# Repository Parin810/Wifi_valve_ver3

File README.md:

### Solar Harvesting IoT based Irrigation valve:
This repo contains all the necessary hardware and software information about IoT/Wifi Actuator that has the following features:
1. ESP8266 as the controller/radio chip 
2. Uses MQTT as the communication protocol
3. BQ24210 or MCP73831 based solar harvestor
4. Uses Nodemcu custom build firmware
5. Auto modem sleep enabed (DTIM3,4,5)
6. The valve used is a latching solenoid 
7. DRV8832 as driver for latching solenoid
## Resources
The cheapst SOC that supports IEEE 802.11 standard
[ESP8266](https://tttapa.github.io/ESP8266/Chap04%20-%20Microcontroller.html)

Lua based firmware to simplify application programming
[Nodemcu - Lua](https://nodemcu.readthedocs.io/en/master/)

ESP8266 power consumption
[ESP8266 current profile](https://jeelabs.org/book/1526f/)

## Major Components Used 
(click to see datasheet)

[ESP8266-07](https://www.mikrocontroller.net/attachment/338570/Ai-thinker_ESP-07_WIFI_Module-EN.pdf)

LDO
[AP2112](https://www.diodes.com/assets/Datasheets/AP2112.pdf)

Lipo/ion charger
[MCP73831](http://ww1.microchip.com/downloads/en/DeviceDoc/20001984g.pdf)

Solar lipo/ion charger 
[BQ24210](http://www.ti.com/lit/ds/symlink/bq24210.pdf)

PMOS switch 
[PMV65XP](https://assets.nexperia.com/documents/data-sheet/PMV65XP.pdf)

## Loading LUA firmware
Download Nodemcu flasher from [here](https://github.com/nodemcu/nodemcu-flasher). for windows. For Linux use esptool.py (see repository for details)
Look at this [page](https://nodemcu.readthedocs.io/en/master/en/flash/) from nodemcu lua documentation

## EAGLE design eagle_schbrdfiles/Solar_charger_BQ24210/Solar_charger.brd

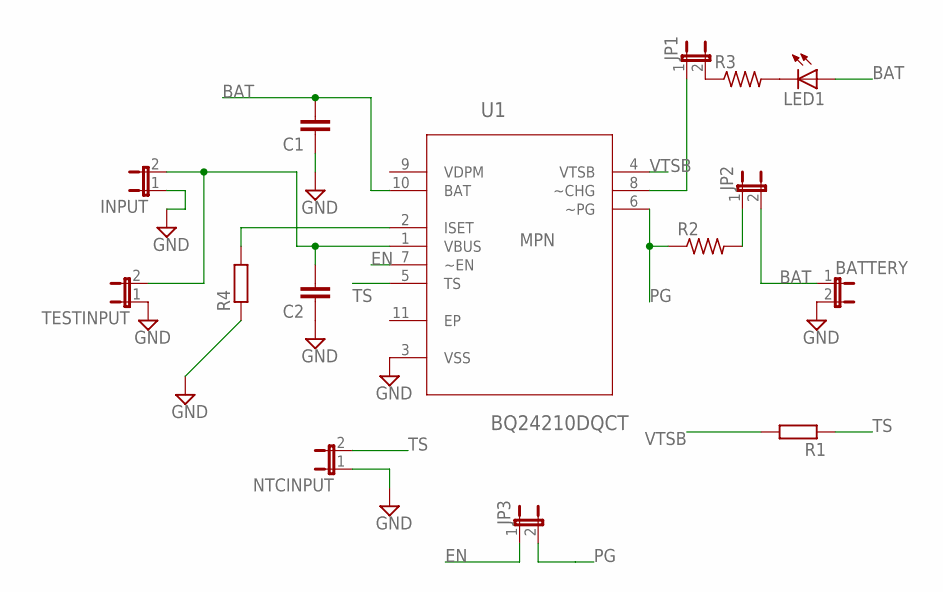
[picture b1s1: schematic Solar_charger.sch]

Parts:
BATTERY: JP1E; JP1
C1, C2: C2,5-3; C2.5-3
INPUT: JP1E; JP1
JP1, JP2, JP3: JP1E; JP1
LED1: LED5MM
NTCINPUT: JP1E; JP1
R1, R4: R-EU_0204/7; 0204/7
R2, R3: R-US_M1206; M1206
TESTINPUT: JP1E; JP1
U1: BQ24210DQCT; SON50P200X300X80-11N

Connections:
BAT: BATTERY.1, C1.2, JP2.2, LED1.A, U1.10 (BAT)
EN: JP3.1, U1.7 (~EN)
GND: BATTERY.2, C1.1, C2.1, INPUT.1, NTCINPUT.1, R4.1, U1.3 (VSS)
unnamed: C2.2, INPUT.2, TESTINPUT.2, U1.1 (VBUS)
unnamed: R4.2, U1.2 (ISET)
unnamed: JP2.1, R2.2
unnamed: LED1.K (C), R3.2
unnamed: JP1.1, U1.8 (~CHG)
unnamed: JP1.2, R3.1
PG: JP3.2, R2.1, U1.6 (~PG)
TS: NTCINPUT.2, R1.1, U1.5 (TS)
VTSB: R1.2, U1.4 (VTSB)

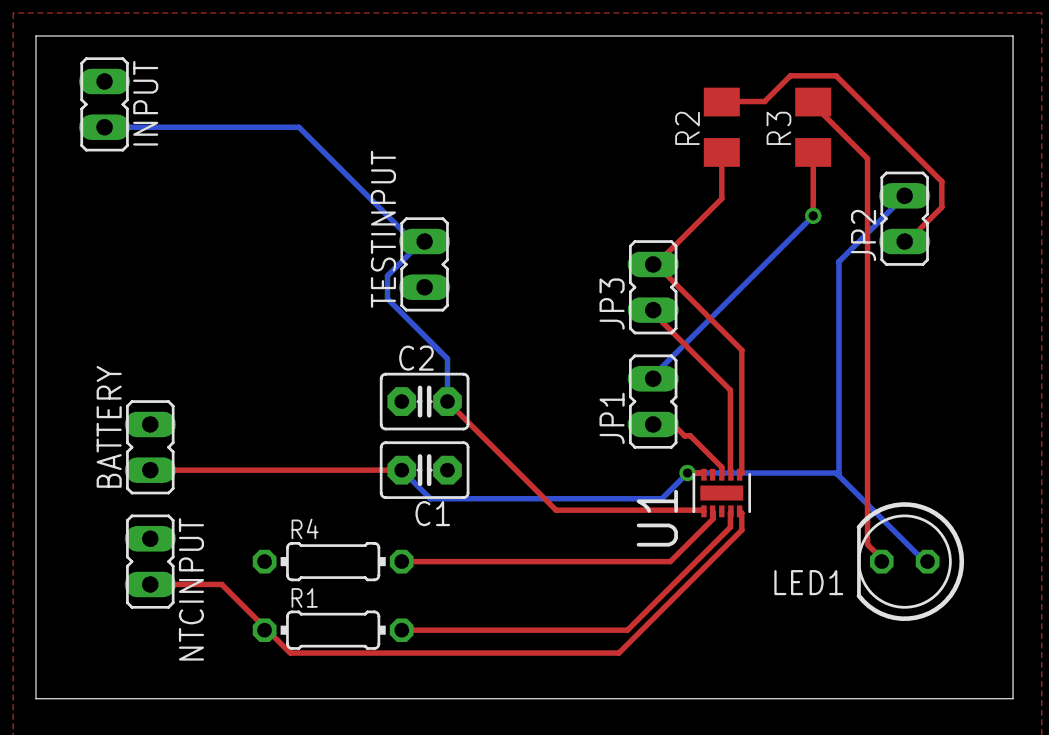
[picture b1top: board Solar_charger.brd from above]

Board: 2 copper layers, 54.3 x 36.8 mm, 15 parts (0 on the bottom side), 12 nets.

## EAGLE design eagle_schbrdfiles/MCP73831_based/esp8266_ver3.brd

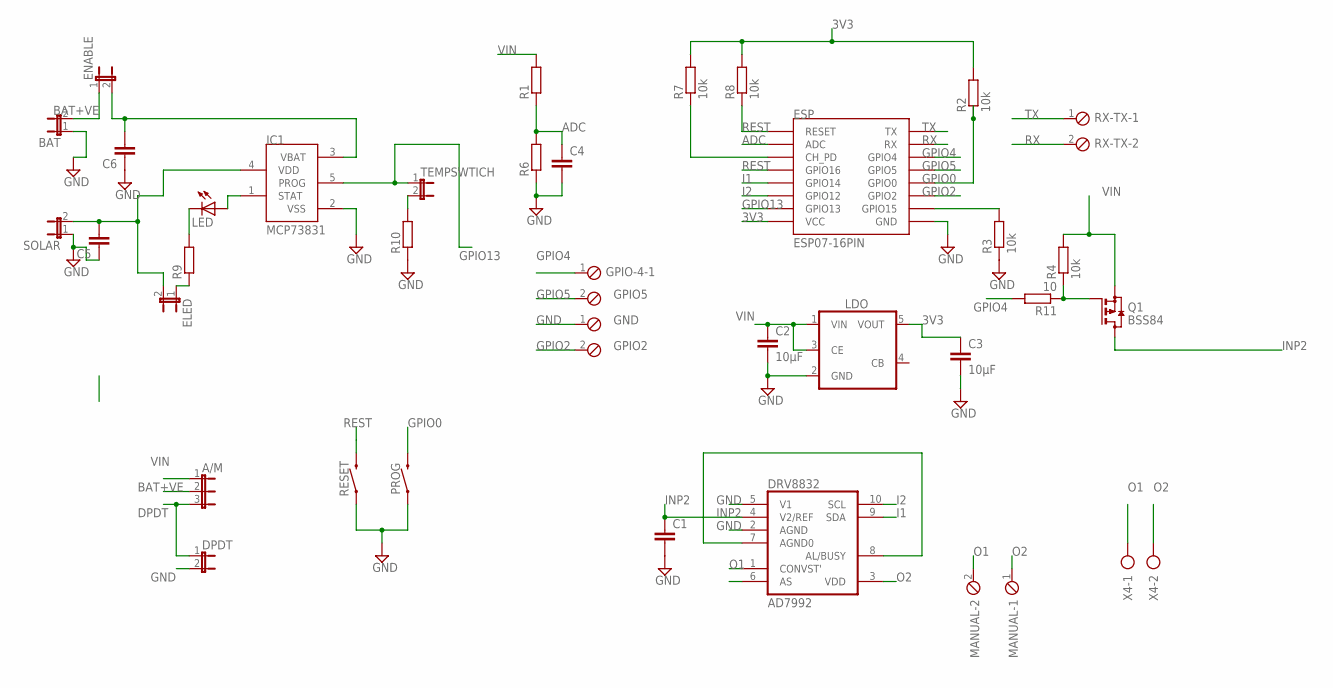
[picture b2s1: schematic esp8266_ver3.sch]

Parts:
A/M: JP2E; JP2
BAT: JP1E; JP1
C1: C-EUC0805K; C0805K
C2, C3: 10μF; C1206
C4, C5, C6: C-EUC1206; C1206
DPDT: JP1E; JP1
DRV8832: AD7992; MSOP10
ELED: JP1E; JP1
ENABLE: JP1E; JP1
ESP: ESP07-16PIN
GPIO-4: MPT2; 2POL254
IC1: MCP73831; SOT23-5L
LDO: TS5205; SOT25
LED: LED_E; LED_1206
MANUAL: MPT2; 2POL254
PROG: MOMENTARY-SWITCH-SPST-SMD-5.2MM; TACTILE_SWITCH_SMD_5.2MM
Q1: BSS84; SOT23
R1, R6, R9, R10: R-EU_R1206; R1206
R2, R3, R4, R7, R8: 10k; R1206
R11: 10; R1206
RESET: MOMENTARY-SWITCH-SPST-SMD-5.2MM; TACTILE_SWITCH_SMD_5.2MM
RX-TX: MPT2; 2POL254
SOLAR: JP1E; JP1
TEMPSWTICH: JP1E; JP1
X2: MPT2; 2POL254
X4: AK300/2

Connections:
3V3: C3.1, ESP.VCC, LDO.5 (VOUT), R2.2, R7.2, R8.2
ADC: C4.1, ESP.ADC, R1.1, R6.2
B: C6.2, ENABLE.2, IC1.3 (VBAT)
BAT+VE: A/M.2, BAT.2, ENABLE.1
DPDT: A/M.3, DPDT.1
GND: BAT.1, C1.2, C2.2, C3.2, C4.2, C5.1, C6.1, DPDT.2, DRV8832.2 (AGND), DRV8832.5 (V1), ESP.GND, IC1.2 (VSS), LDO.2 (GND), PROG.1, R3.1, R6.1, R10.1, RESET.1, SOLAR.1, X2.1
GPIO0: ESP.GPIO0, PROG.3 (2), R2.1
GPIO2: ESP.GPIO2, X2.2
GPIO4: ESP.GPIO4, GPIO-4.1, R11.2
GPIO5: ESP.GPIO5, GPIO-4.2
GPIO13: ESP.GPIO13, IC1.5 (PROG), TEMPSWTICH.1
I1: DRV8832.9 (SDA), ESP.GPIO14
I2: DRV8832.10 (SCL), ESP.GPIO12
INP2: C1.1, DRV8832.4 (V2/REF), Q1.3 (D)
unnamed: IC1.1 (STAT), LED.A
unnamed: DRV8832.7 (AGND0), DRV8832.8 (AL/BUSY)
unnamed: R10.2, TEMPSWTICH.2
unnamed: LED.C, R9.2
unnamed: ELED.1, R9.1
unnamed: Q1.1 (G), R4.1, R11.1
unnamed: C5.2, ELED.2, IC1.4 (VDD), SOLAR.2
unnamed: ESP.CH_PD, R7.1
unnamed: ESP.GPIO15, R3.2
O1: DRV8832.1 (CONVST'), MANUAL.2, X4.1
O2: DRV8832.3 (VDD), MANUAL.1, X4.2
REST: ESP.GPIO16, ESP.REST (RESET), R8.1, RESET.3 (2)
RX: ESP.RX, RX-TX.2
TX: ESP.TX, RX-TX.1
VIN: A/M.1, C2.1, LDO.1 (VIN), LDO.3 (CE), Q1.2 (S), R1.2, R4.2

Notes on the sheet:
GPIO5
GND
GPIO2

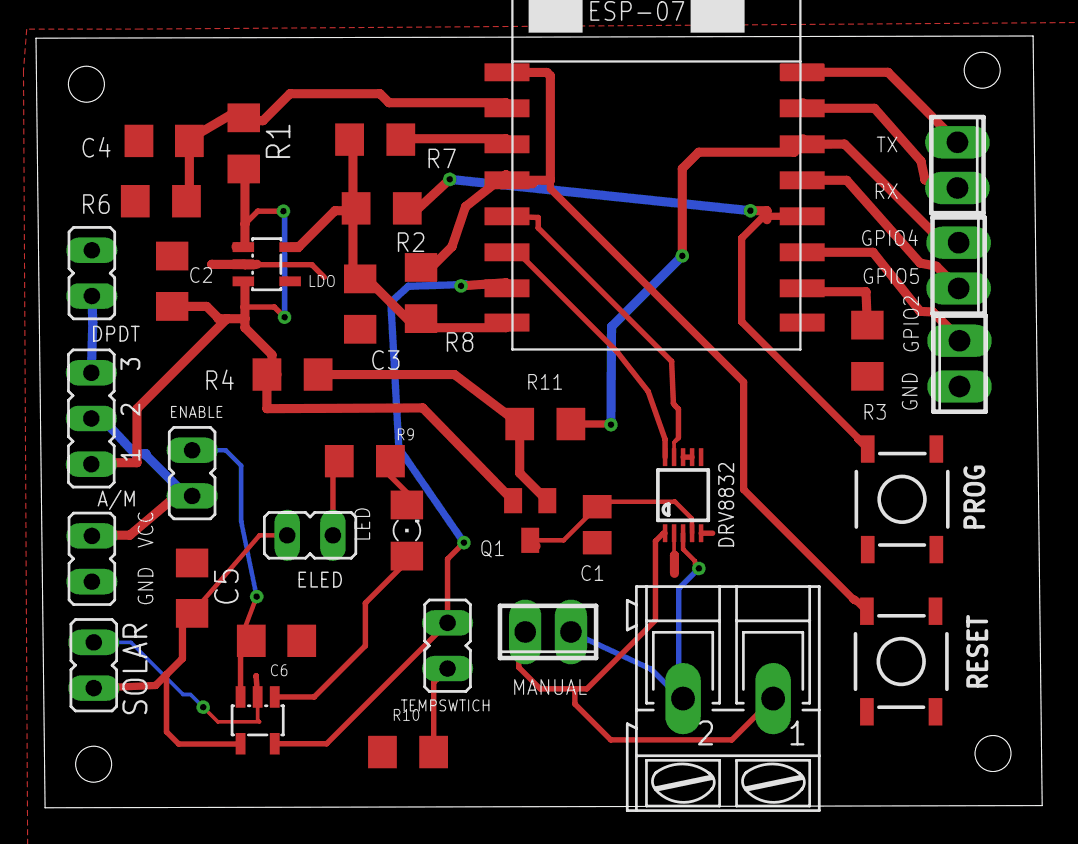
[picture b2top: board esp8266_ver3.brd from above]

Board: 2 copper layers, 55.9 x 42.9 mm, 36 parts (0 on the bottom side), 29 nets.

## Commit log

2018-06-16 new version with irrigation time
2018-06-16 added connect1.lua
2018-06-16 sorted time issues
2018-07-12 script with comments
2018-07-12 changes directory structure
2018-07-12 added nodemcu firmware
2018-07-13 added more details
2018-07-13 changes in init.lua
2018-07-13 final scripts
2018-07-18 added sch brd files
2018-07-18 added schematic and brd files
2018-07-18 added ppt
2018-07-18 added bom
2018-07-19 added older versions of code
2018-07-22 added python scripts
2018-07-24 added images
2018-07-24 added board images
2018-07-26 added eagle schematics

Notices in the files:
parts and their libraries:
SparkFun-Switches: Licensing: Creative Commons ShareAlike 4.0 International - https://creativecommons.org/licenses/by-sa/4.0
